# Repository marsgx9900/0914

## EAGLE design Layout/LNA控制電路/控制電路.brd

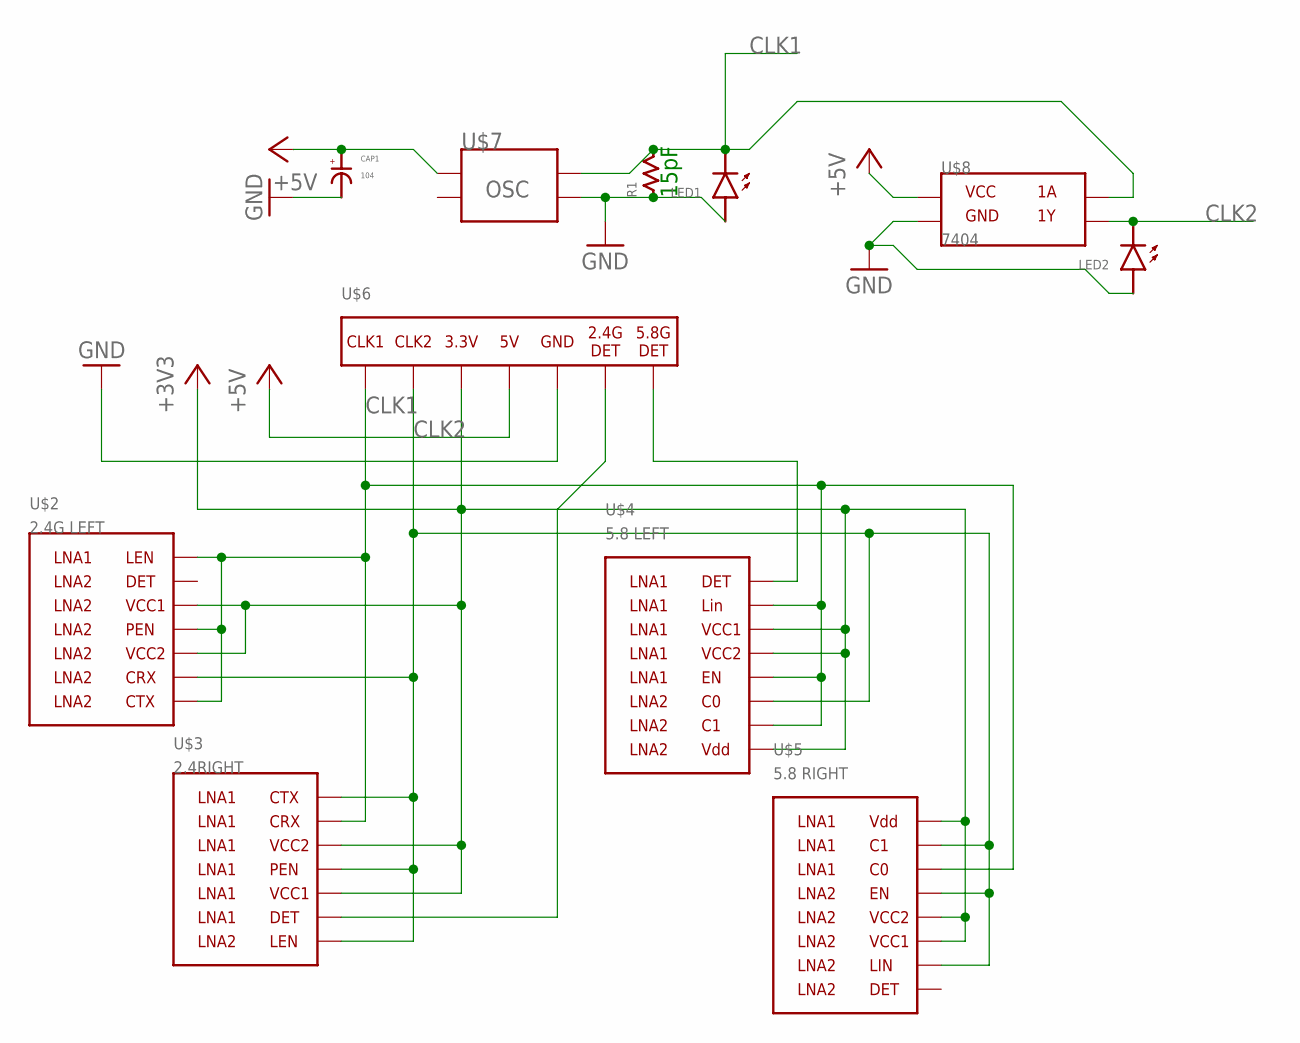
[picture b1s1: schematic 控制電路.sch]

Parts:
CAP1: 104; CAP-100MIL
LED1, LED2: LED-5MM; 2-PIN-200MIL-LED
R1: RESISTOR-200MIL
U$2: PROJECT-2.4G-LEFTSIDE
U$3: PROJECT-2.4G-RIGHTSIDE
U$4: PROJECT-5G-LEFTSIDE
U$5: PROJECT-5G-RIGHTSIDE
U$6: PROJECT-IO
U$7: PROJECT-CRYSTAL
U$8: PROJECT-7404

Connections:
+3V3: U$2.VCC1, U$2.VCC2, U$3.VCC1, U$3.VCC2, U$4.VCC1, U$4.VCC2, U$4.VDD, U$5.VCC1, U$5.VCC2, U$5.VDD, U$6.3.3V
+5V: CAP1.P$1, U$6.5V, U$7.P$1, U$8.P$14
CLK1: LED1.L- (LED-), R1.P$2, U$2.CTX, U$2.LEN, U$2.PEN, U$3.CRX, U$4.C1, U$4.EN, U$4.LIN, U$5.C0, U$6.CLK1, U$7.P$4, U$8.P$1
CLK2: LED2.L- (LED-), U$2.CRX, U$3.CTX, U$3.LEN, U$3.PEN, U$4.C0, U$5.C1, U$5.EN, U$5.LIN, U$6.CLK2, U$8.P$2
GND: CAP1.P$2, LED1.L+ (LED+), LED2.L+ (LED+), R1.P$1, U$6.GND, U$7.P$3, U$8.P$7
unnamed: U$3.DET, U$6.2.4DET
unnamed: U$4.DET, U$6.5.8DET

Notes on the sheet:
15pF

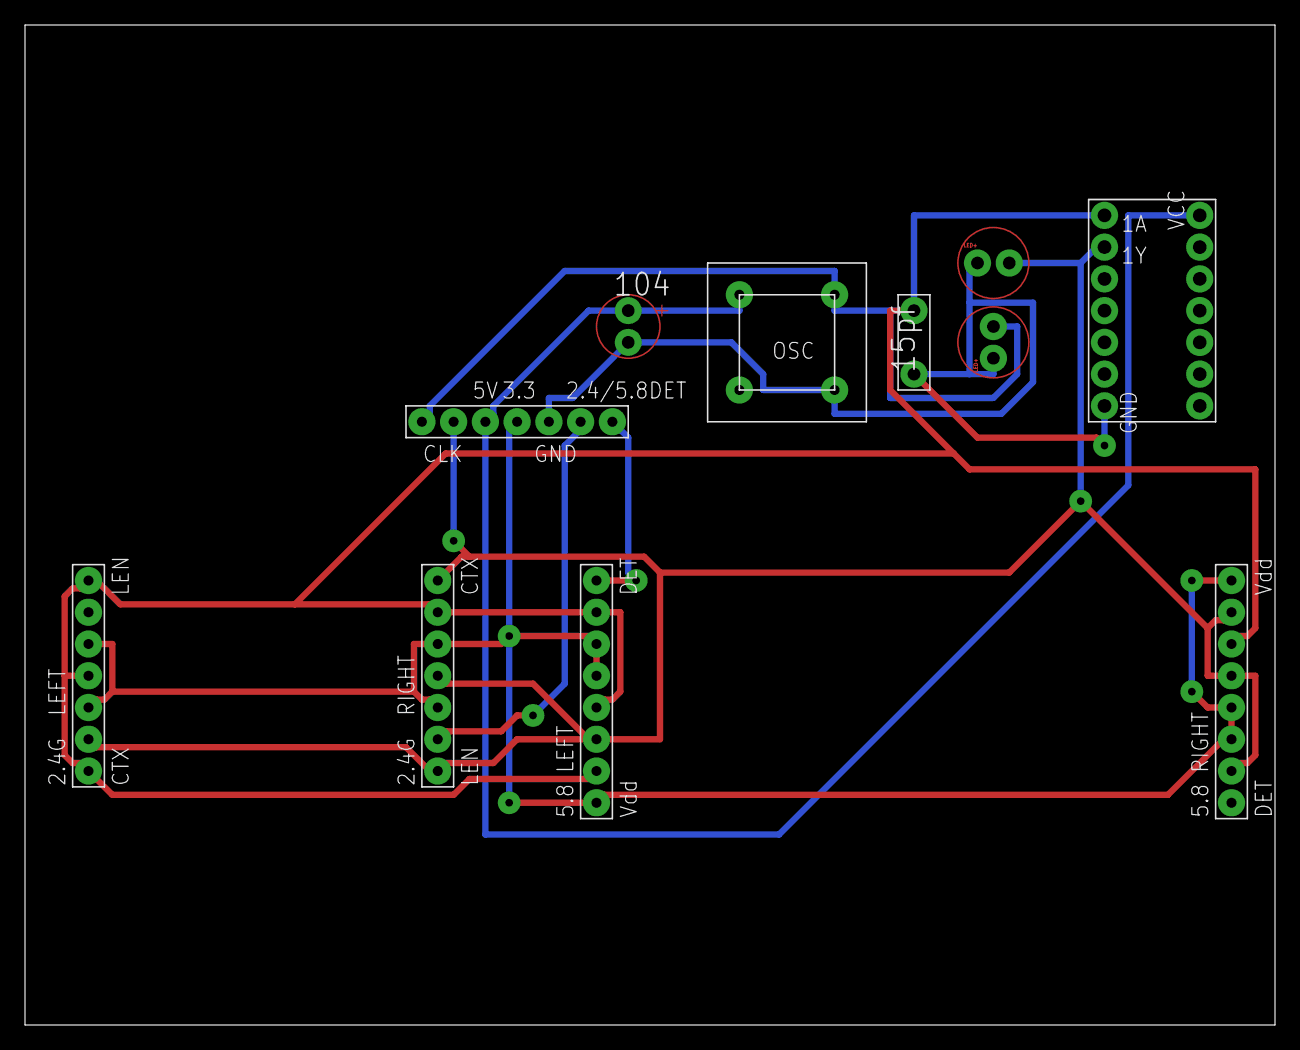
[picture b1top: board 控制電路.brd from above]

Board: 2 copper layers, 100.0 x 80.0 mm, 11 parts (0 on the bottom side), 7 nets.

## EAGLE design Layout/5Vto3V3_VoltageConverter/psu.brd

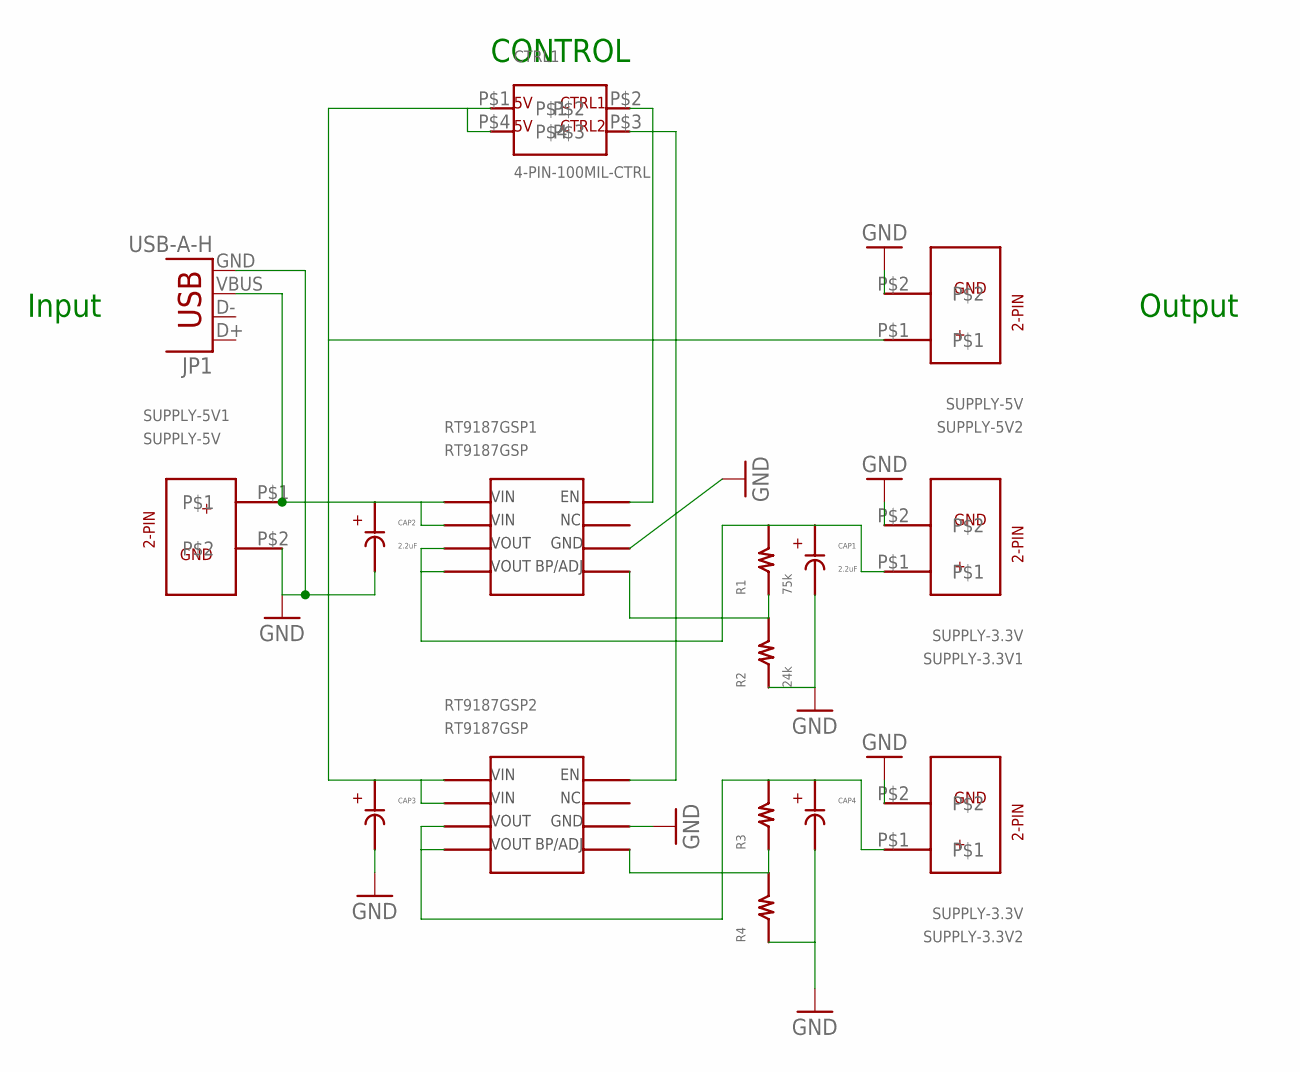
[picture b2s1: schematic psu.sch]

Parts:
CAP1, CAP2: 2.2uF; CAP-100MIL
CAP3, CAP4: CAP-100MIL
CTRL1: 4-PIN-100MIL-CTRL
JP1: USB-A-H
R1: 75k; RESISTOR-SMD-1206
R2: 24k; RESISTOR-SMD-1206
R3, R4: RESISTOR-SMD-1206
RT9187GSP1, RT9187GSP2: RT9187GSP; SOP-8
SUPPLY-3.3V1, SUPPLY-3.3V2: SUPPLY-3.3V; 2-PIN-100MIL-3.3V
SUPPLY-5V1, SUPPLY-5V2: SUPPLY-5V; 2-PIN-100MIL-5V

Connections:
GND: CAP1.P$2, CAP2.P$2, CAP3.P$2, CAP4.P$2, JP1.GND, R2.P$1, R4.P$1, RT9187GSP1.P$6, RT9187GSP2.P$6, SUPPLY-3.3V1.P$2, SUPPLY-3.3V2.P$2, SUPPLY-5V1.P$2, SUPPLY-5V2.P$2
unnamed: R1.P$1, R2.P$2, RT9187GSP1.P$5
unnamed: CTRL1.P$2, RT9187GSP1.P$8
unnamed: CAP1.P$1, R1.P$2, RT9187GSP1.P$3, RT9187GSP1.P$4, SUPPLY-3.3V1.P$1
unnamed: CAP4.P$1, R3.P$2, RT9187GSP2.P$3, RT9187GSP2.P$4, SUPPLY-3.3V2.P$1
unnamed: R3.P$1, R4.P$2, RT9187GSP2.P$5
unnamed: CTRL1.P$3, RT9187GSP2.P$8
unnamed: CAP2.P$1, CAP3.P$1, CTRL1.P$1, CTRL1.P$4, JP1.VBUS, RT9187GSP1.P$1, RT9187GSP1.P$2, RT9187GSP2.P$1, RT9187GSP2.P$2, SUPPLY-5V1.P$1, SUPPLY-5V2.P$1

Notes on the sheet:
Input
Output
CONTROL

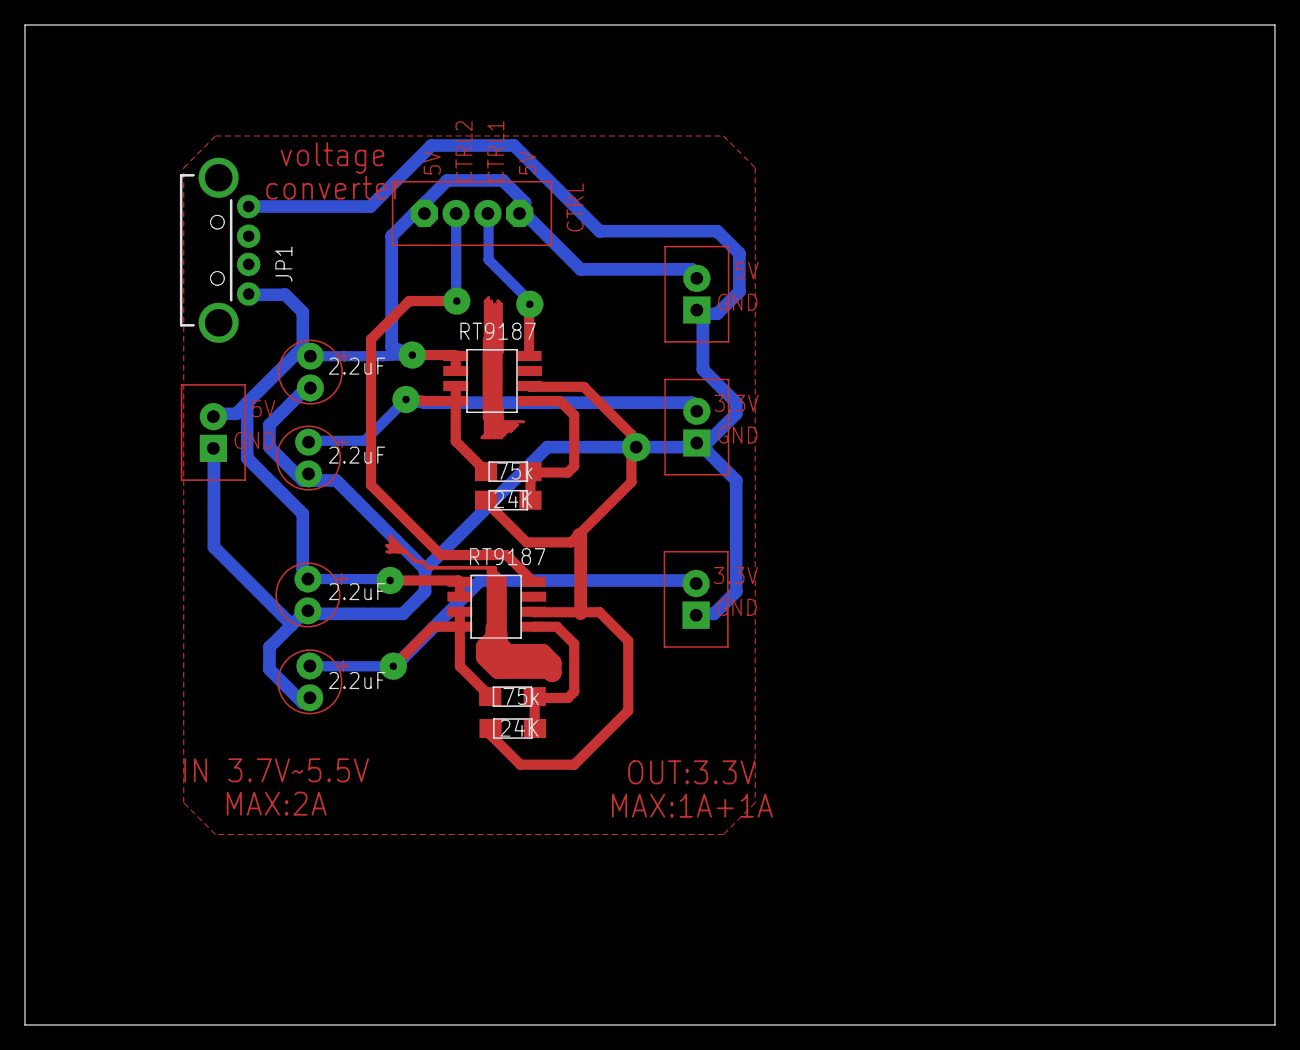
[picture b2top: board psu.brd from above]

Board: 2 copper layers, 100.0 x 80.0 mm, 16 parts (0 on the bottom side), 8 nets.

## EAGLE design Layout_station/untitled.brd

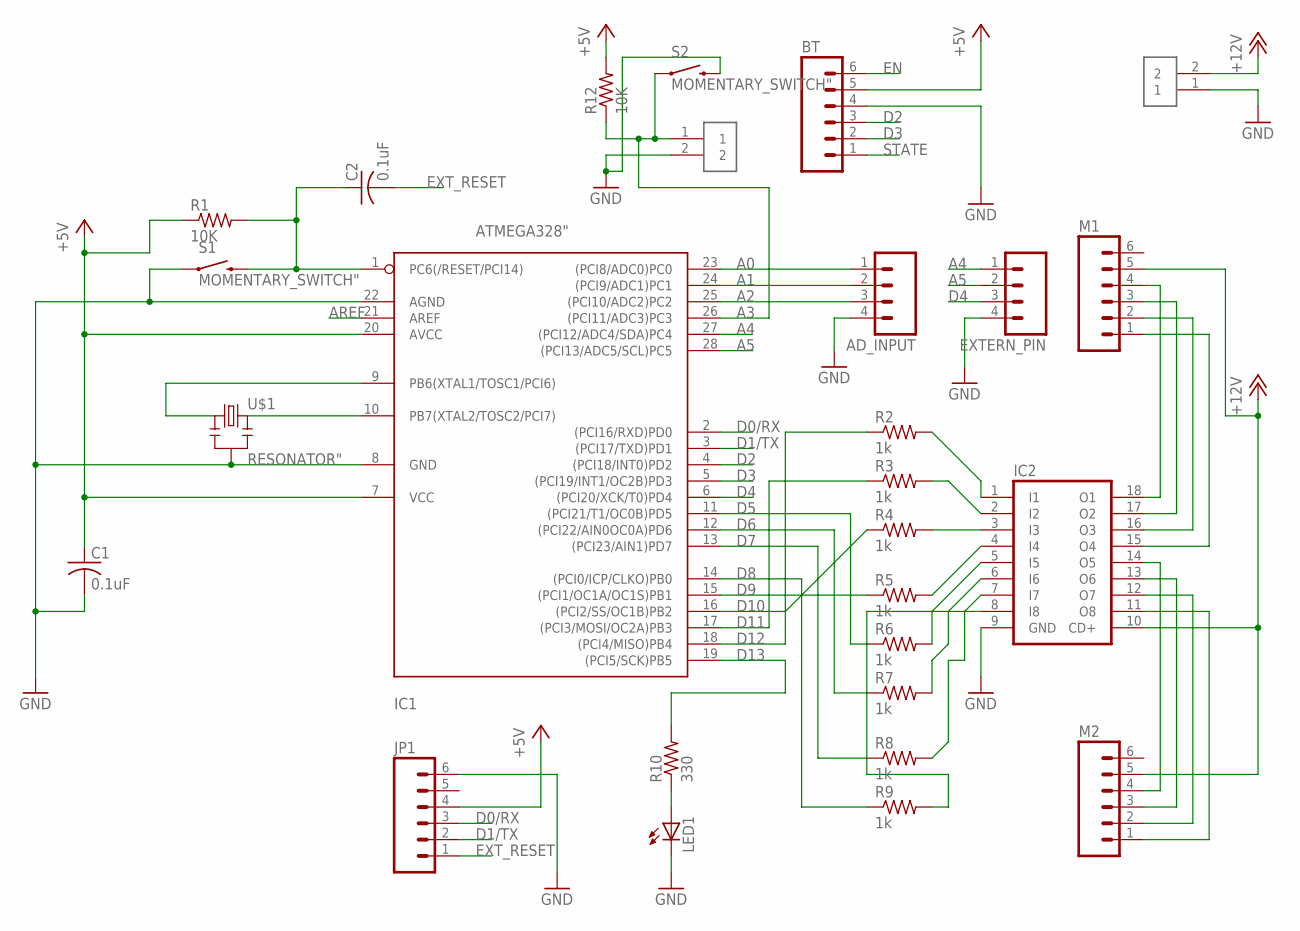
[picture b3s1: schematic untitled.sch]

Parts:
12V_INPUT: 1X02_HEADER
AD_INPUT: 1X04_HEADER"; 1X04_HEADER
BT: 1X06_HEADER"; 1X06_HEADER
C1, C2: 0.1uF; UNPOLARIZED_CAP
EXTERN_PIN: 1X04_HEADER"; 1X04_HEADER
IC1: ATMEGA328"; ATMEGA328
IC2: ULN2803A; DIL18
JP1: 1X06_HEADER"; 1X06_HEADER
LED1: LED3MM; LED
LIMIT_SW: 1X02_HEADER
M1, M2: 1X06_HEADER"; 1X06_HEADER
R1, R12: 10K; RESISTOR
R2, R3, R4, R5, R6, R7, R8, R9: 1k; RESISTOR
R10: 330; RESISTOR
S1, S2: MOMENTARY_SWITCH"; MOMENTARY_SWITCH
U$1: RESONATOR"; RESONATOR

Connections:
+5V: BT.5, C1.1, IC1.7 (VCC), IC1.20 (AVCC), JP1.4, R1.1, R12.2
+12V: 12V_INPUT.2, IC2.10 (CD+), M1.5, M2.5
A0: AD_INPUT.1, IC1.23 ((PCI8/ADC0)PC0)
A1: AD_INPUT.2, IC1.24 ((PCI9/ADC1)PC1)
A2: AD_INPUT.3, IC1.25 ((PCI10/ADC2)PC2)
A3: IC1.26 ((PCI11/ADC3)PC3), LIMIT_SW.1, R12.1, S2.1
A4: EXTERN_PIN.1, IC1.27 ((PCI12/ADC4/SDA)PC4)
A5: EXTERN_PIN.2, IC1.28 ((PCI13/ADC5/SCL)PC5)
AREF: IC1.21 (AREF)
D0/RX: IC1.2 ((PCI16/RXD)PD0), JP1.3
D1/TX: IC1.3 ((PCI17/TXD)PD1), JP1.2
D2: BT.3, IC1.4 ((PCI18/INT0)PD2)
D3: BT.2, IC1.5 ((PCI19/INT1/OC2B)PD3)
D4: EXTERN_PIN.3, IC1.6 ((PCI20/XCK/T0)PD4)
D5: IC1.11 ((PCI21/T1/OC0B)PD5), R6.1
D6: IC1.12 ((PCI22/AIN0OC0A)PD6), R7.1
D7: IC1.13 ((PCI23/AIN1)PD7), R8.1
D8: IC1.14 ((PCI0/ICP/CLKO)PB0), R9.1
D9: IC1.15 ((PCI1/OC1A/OC1S)PB1), R5.1
D10: IC1.16 ((PCI2/SS/OC1B)PB2), R4.1
D11: IC1.17 ((PCI3/MOSI/OC2A)PB3), R3.1
D12: IC1.18 ((PCI4/MISO)PB4), R2.1
D13: IC1.19 ((PCI5/SCK)PB5), R10.2
EN: BT.6
EXT_RESET: C2.2, JP1.1
GND: 12V_INPUT.1, AD_INPUT.4, BT.4, C1.2, EXTERN_PIN.4, IC1.8 (GND), IC1.22 (AGND), IC2.9 (GND), JP1.6, LED1.K (C), LIMIT_SW.2, S1.1, S2.3 (2), U$1.2
unnamed: IC1.9 (PB6(XTAL1/TOSC1/PCI6)), U$1.1
unnamed: IC1.10 (PB7(XTAL2/TOSC2/PCI7)), U$1.3
unnamed: C2.1, IC1.1 (PC6(/RESET/PCI14)), R1.2, S1.3 (2)
unnamed: IC2.1 (I1), R2.2
unnamed: IC2.2 (I2), R3.2
unnamed: IC2.3 (I3), R4.2
unnamed: IC2.4 (I4), R5.2
unnamed: IC2.5 (I5), R6.2
unnamed: IC2.6 (I6), R7.2
unnamed: IC2.7 (I7), R8.2
unnamed: IC2.8 (I8), R9.2
unnamed: IC2.18 (O1), M1.4
unnamed: IC2.17 (O2), M1.3
unnamed: IC2.16 (O3), M1.2
unnamed: IC2.15 (O4), M1.1
unnamed: IC2.14 (O5), M2.4
unnamed: IC2.13 (O6), M2.3
unnamed: IC2.12 (O7), M2.2
unnamed: IC2.11 (O8), M2.1
unnamed: LED1.A, R10.1
STATE: BT.1

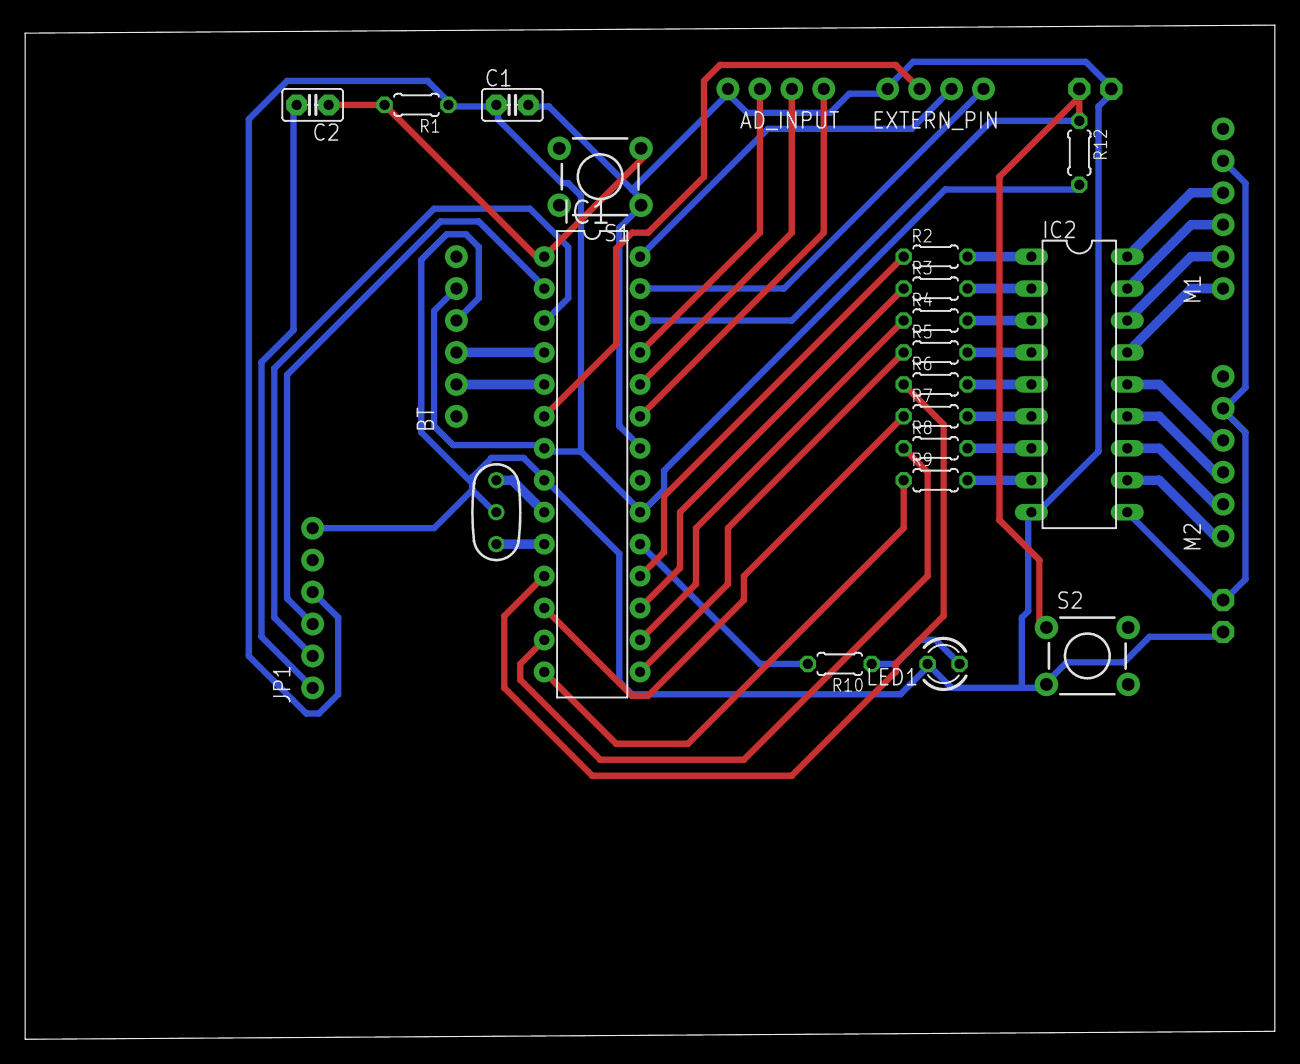
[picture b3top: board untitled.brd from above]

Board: 2 copper layers, 99.4 x 80.6 mm, 27 parts (0 on the bottom side), 44 nets.

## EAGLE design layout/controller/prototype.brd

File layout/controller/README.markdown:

Layout image
----------
* [上板 top.pdf]
* [下版 bottom.pdf]

Reference
----------
* [Eagle Layout教學](http://www.makezine.com.tw/make2599131456/105)
* [RBBB元件庫](http://www.moderndevice.com/downloads)

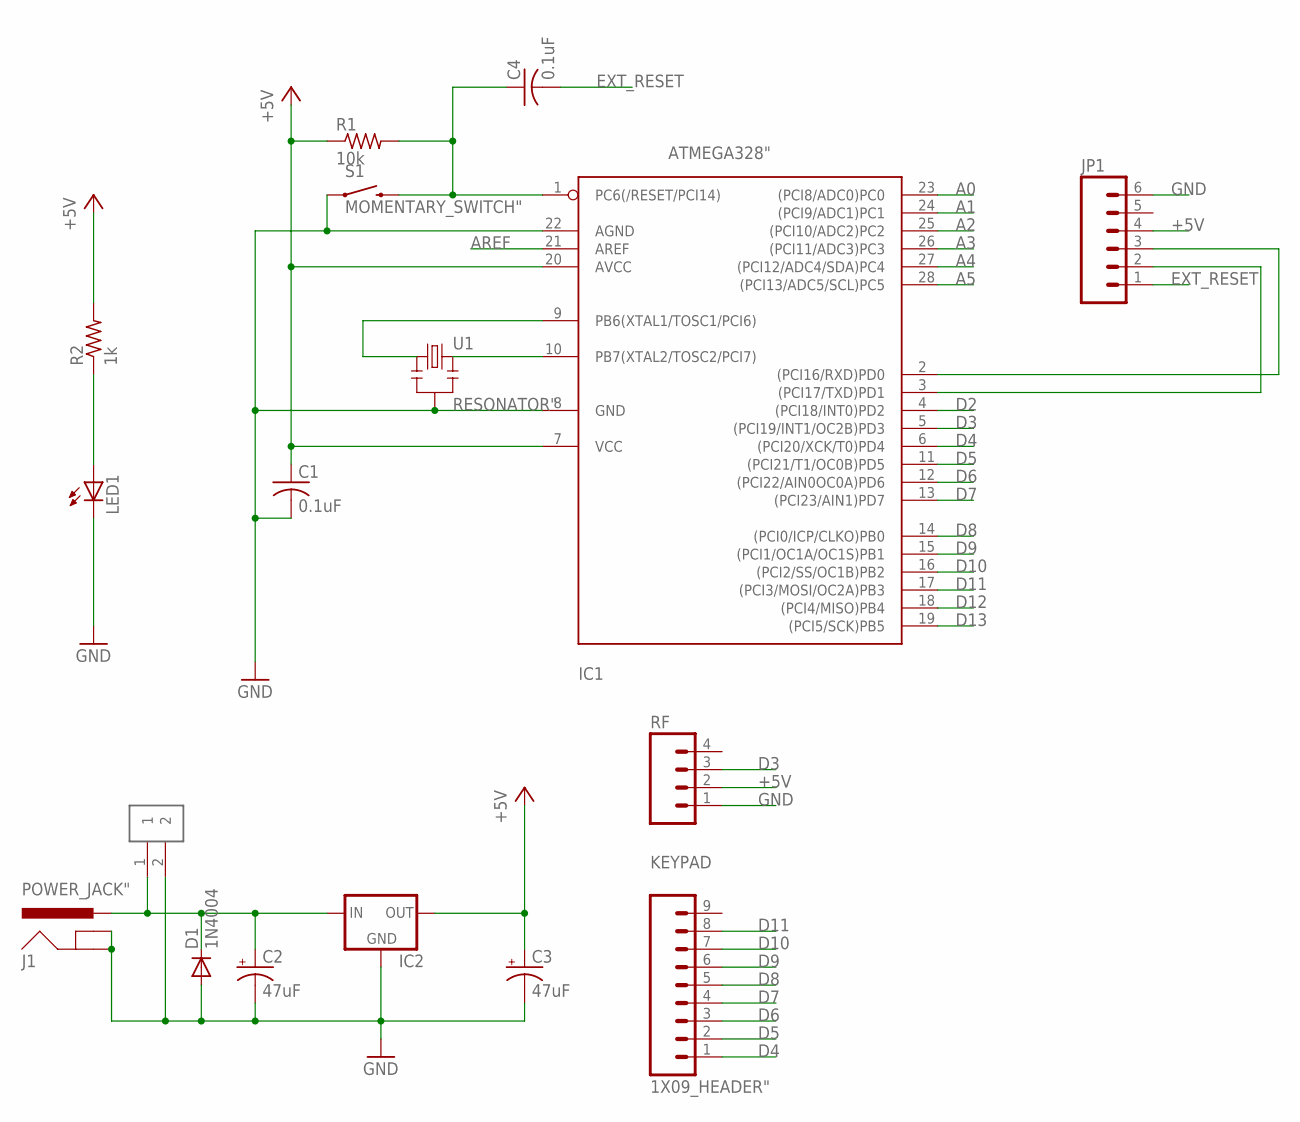
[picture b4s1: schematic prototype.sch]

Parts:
C1, C4: 0.1uF; UNPOLARIZED_CAP
C2, C3: 47uF; ELECTROLYTIC_CAP
D1: 1N4004; DO41-10
IC1: ATMEGA328"; ATMEGA328
IC2: REGULATOR; L4931_REGULATOR
J1: POWER_JACK"; POWER_JACK
JP1: 1X06_HEADER"; 1X06_HEADER
KEYPAD: 1X09_HEADER"; 1X09_HEADER
LED1: LED3MM; LED
R1: 10k; RESISTOR
R2: 1k; RESISTOR
RF: 1X04_HEADER"; 1X04_HEADER
S1: MOMENTARY_SWITCH"; MOMENTARY_SWITCH
U1: RESONATOR"; RESONATOR
U$1: 1X02_HEADER

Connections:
+5V: C1.1, C3.+, IC1.7 (VCC), IC1.20 (AVCC), IC2.OUT, JP1.4, R1.1, R2.2, RF.2
A0: IC1.23 ((PCI8/ADC0)PC0)
A1: IC1.24 ((PCI9/ADC1)PC1)
A2: IC1.25 ((PCI10/ADC2)PC2)
A3: IC1.26 ((PCI11/ADC3)PC3)
A4: IC1.27 ((PCI12/ADC4/SDA)PC4)
A5: IC1.28 ((PCI13/ADC5/SCL)PC5)
AREF: IC1.21 (AREF)
D2: IC1.4 ((PCI18/INT0)PD2)
D3: IC1.5 ((PCI19/INT1/OC2B)PD3), RF.3
D4: IC1.6 ((PCI20/XCK/T0)PD4), KEYPAD.1
D5: IC1.11 ((PCI21/T1/OC0B)PD5), KEYPAD.2
D6: IC1.12 ((PCI22/AIN0OC0A)PD6), KEYPAD.3
D7: IC1.13 ((PCI23/AIN1)PD7), KEYPAD.4
D8: IC1.14 ((PCI0/ICP/CLKO)PB0), KEYPAD.5
D9: IC1.15 ((PCI1/OC1A/OC1S)PB1), KEYPAD.6
D10: IC1.16 ((PCI2/SS/OC1B)PB2), KEYPAD.7
D11: IC1.17 ((PCI3/MOSI/OC2A)PB3), KEYPAD.8
D12: IC1.18 ((PCI4/MISO)PB4)
D13: IC1.19 ((PCI5/SCK)PB5)
EXT_RESET: C4.2, JP1.1
GND: C1.2, C2.-, C3.-, D1.A, IC1.8 (GND), IC1.22 (AGND), IC2.GND, J1.GND, J1.GNDBREAK, JP1.6, LED1.K (C), RF.1, S1.1, U1.2, U$1.2
unnamed: IC1.9 (PB6(XTAL1/TOSC1/PCI6)), U1.1
unnamed: IC1.10 (PB7(XTAL2/TOSC2/PCI7)), U1.3
unnamed: LED1.A, R2.1
unnamed: C4.1, IC1.1 (PC6(/RESET/PCI14)), R1.2, S1.3 (2)
unnamed: C2.+, D1.C, IC2.IN, J1.PWR, U$1.1
unnamed: IC1.2 ((PCI16/RXD)PD0), JP1.3
unnamed: IC1.3 ((PCI17/TXD)PD1), JP1.2

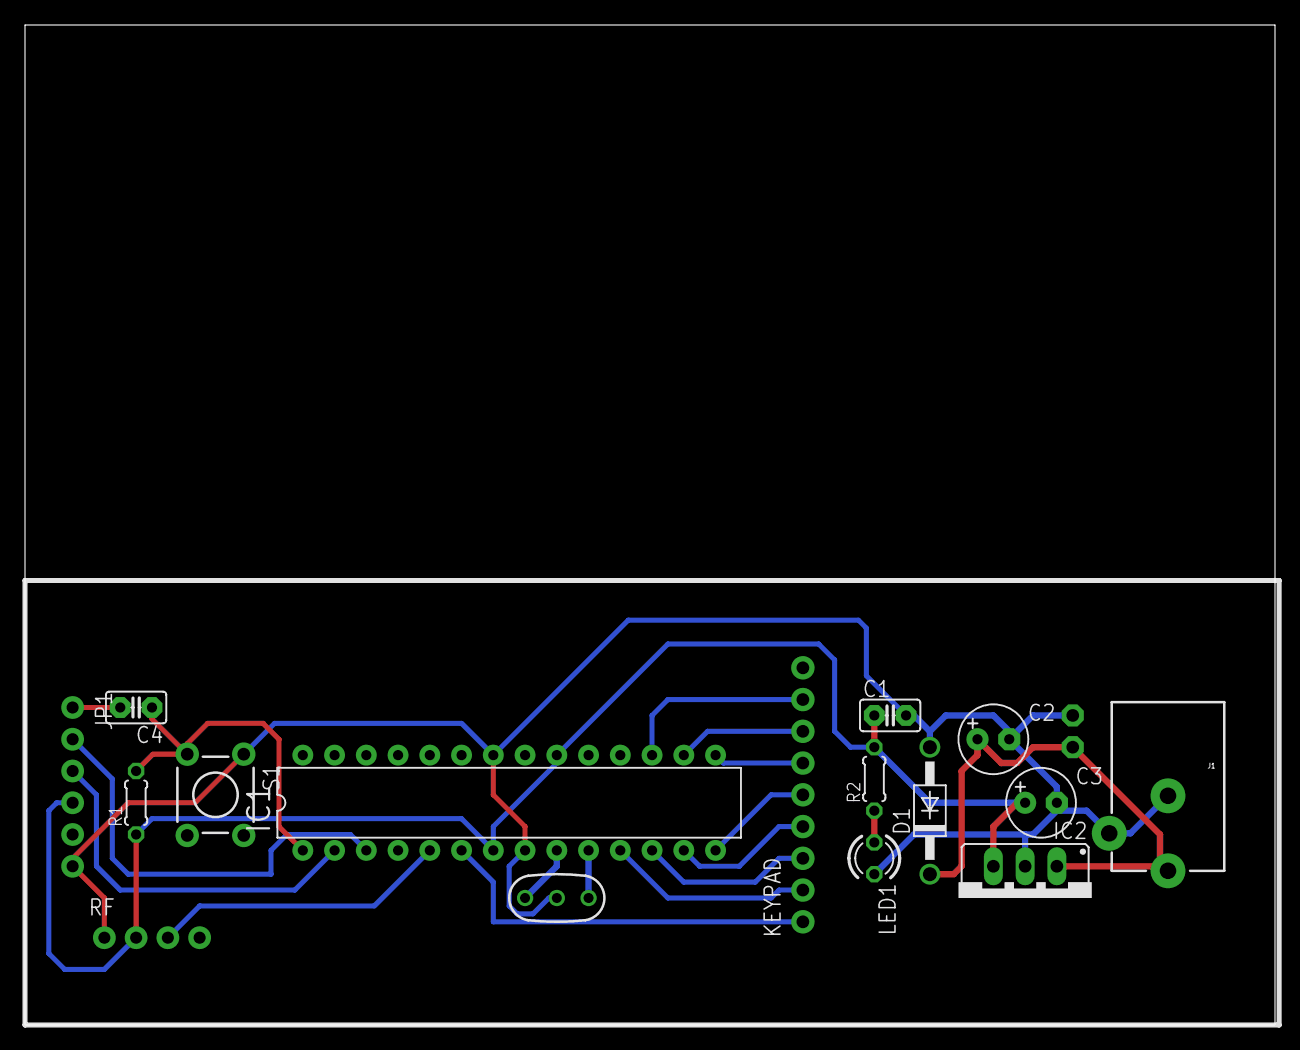
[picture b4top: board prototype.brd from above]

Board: 2 copper layers, 100.0 x 80.0 mm, 17 parts (0 on the bottom side), 19 nets.

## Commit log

2015-09-14 fix bug "no such files or directory"
2015-09-16 remain left&right application
2015-09-16 control: 尚未定義ATmega328鍵盤腳位 station: LEFT&RIGHT尚未實作其功能 func1功能不齊全
2015-09-17 software is done. need to be test.
2015-09-17 nothing
2015-09-17 Release#1 remove "Reset"function
2015-09-17 add layout
2015-09-18 Finish controler layout!
2015-09-18 controler tested on ATmega328 succeed.
2015-09-19 Bluetooth module tested.
2015-09-19 arrangement
2015-09-19 加入說明書
2015-09-19 更多的說明
2015-09-19 none
2015-09-19 加入藍芽，更多的註解 remove SoftReset
2015-09-20 remove RF Function 腳位定義完成
2015-09-20 刪除RF剩餘檔案 加入藍芽控制APP
2015-09-20 modified readme
2015-09-20 remove example
2015-09-20 Copy branch 'addBTinStation' files here
2015-09-22 "Station" layout completed! Readme updated!
2015-09-22 more comment
2015-09-22 Fix comment bug
2015-09-26 1.Add LED Blink 2.雙層板電路測試:正常運作 3.Add pictures.
2015-09-28 加入圖片註解
2015-09-28 comment fix
2015-09-29 add docx
2015-10-13 作品說明書完成
2015-11-15 1.資料夾整理，連同Readme.md圖片路徑改寫 2.加入5Vto3V3變壓器佈線圖
2015-11-15 註解加入eagle使用到的元件庫連結
2015-11-15 修正註解
2015-11-19 添加3v3電壓轉換器usb接頭
2016-01-09 1.2016/1/9成品上電測試失敗 2.新增LNA相關電路檔案
2016-01-09 修改註解
2016-01-14 add final report
2016-01-17 新增藍芽模組工具包

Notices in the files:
parts and their libraries:
SparkFun-Connectors: Licensing: Creative Commons ShareAlike 4.0 International - https://creativecommons.org/licenses/by-sa/4.0
